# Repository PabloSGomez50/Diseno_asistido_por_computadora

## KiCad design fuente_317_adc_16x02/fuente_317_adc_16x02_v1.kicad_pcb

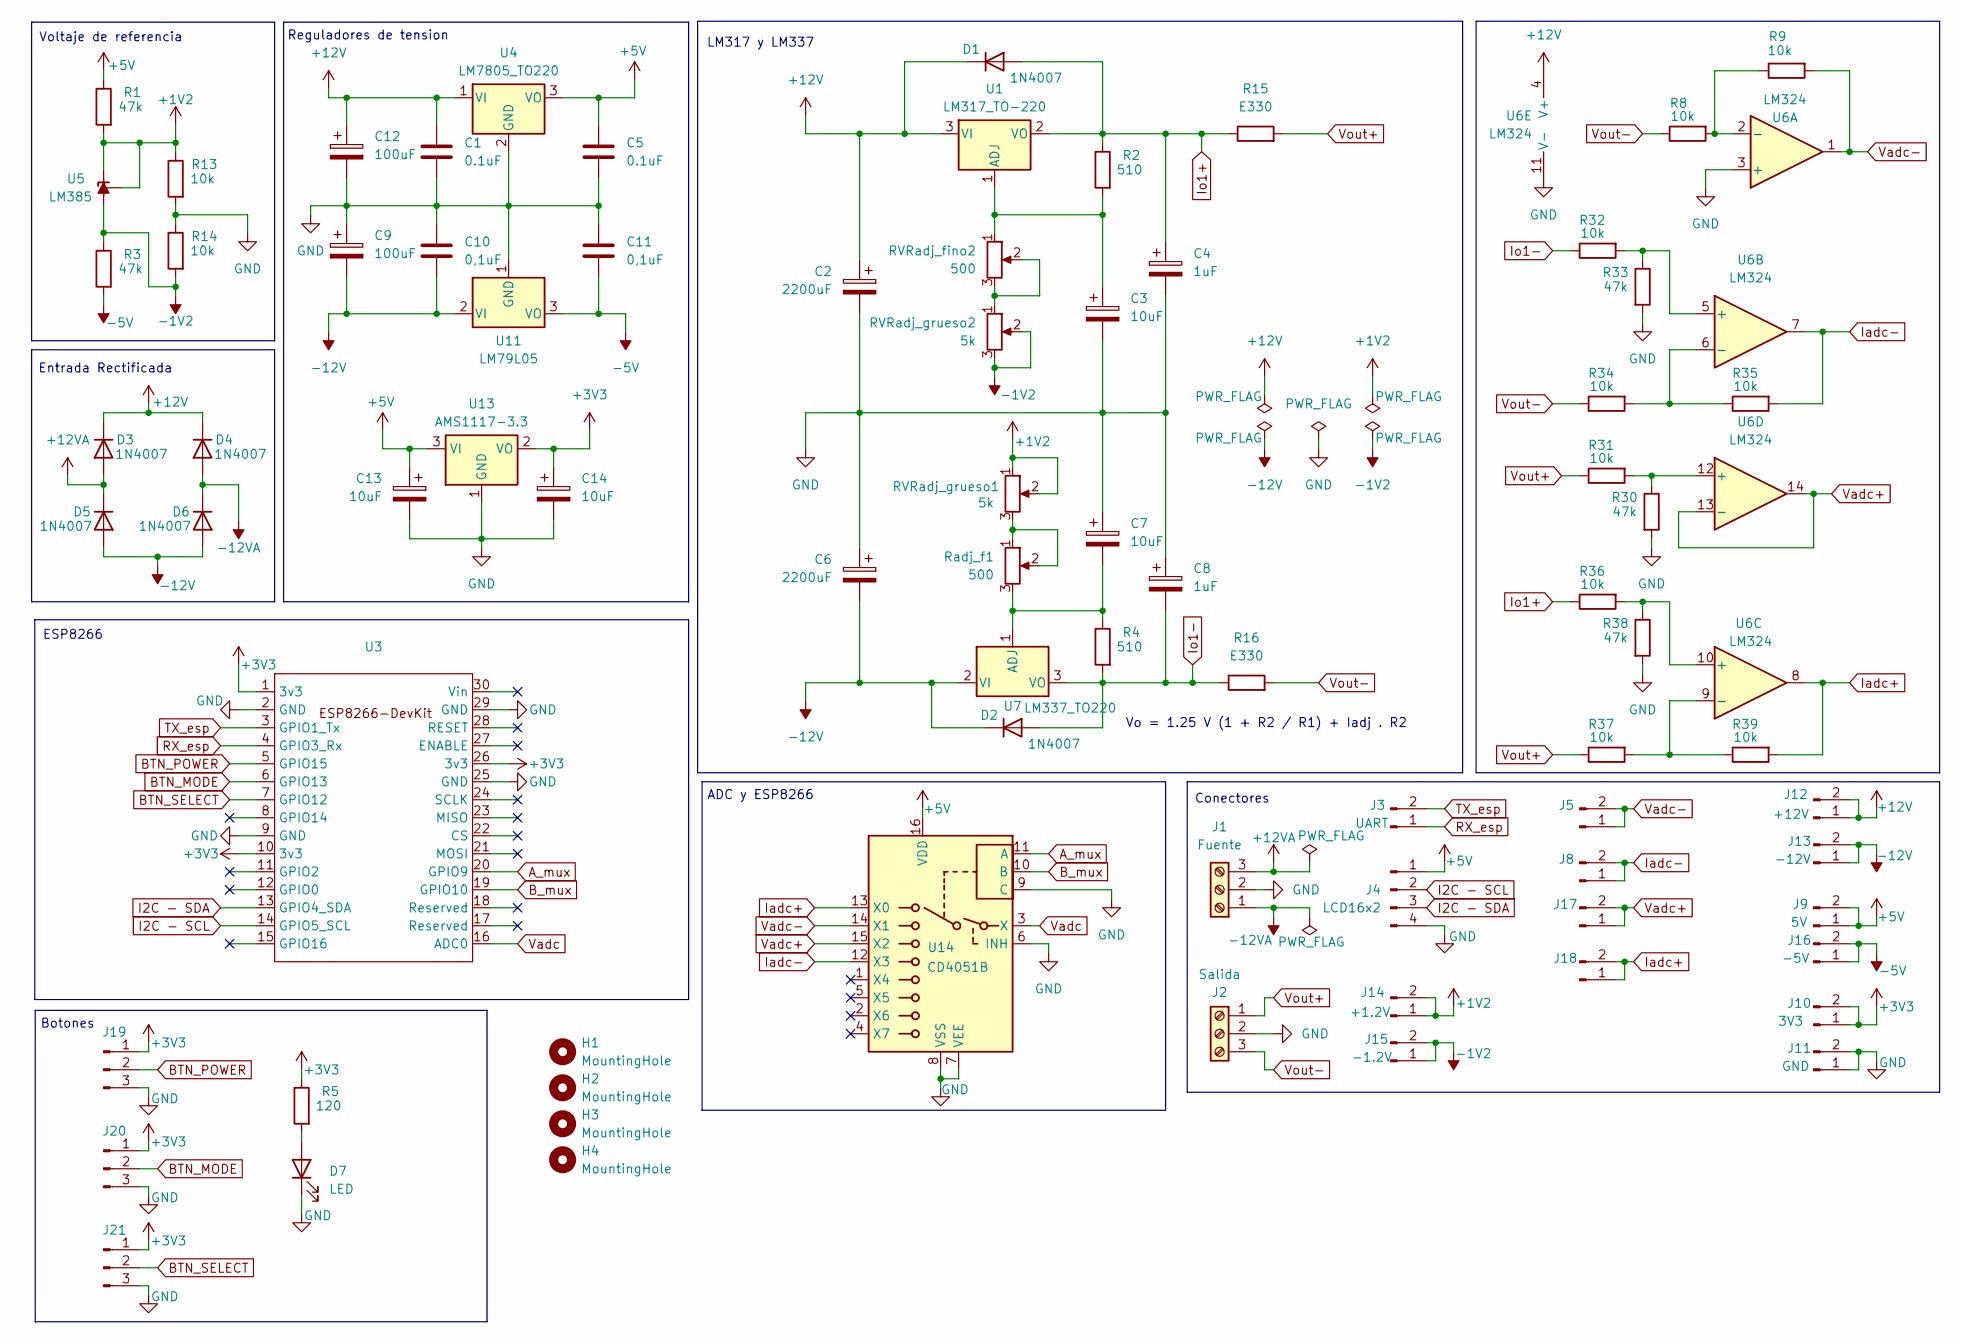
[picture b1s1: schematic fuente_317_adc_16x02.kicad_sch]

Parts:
C1, C5: 0.1uF; C_Disc_D3.0mm_W2.0mm_P2.50mm
C2, C6: 2200uF; CP_Radial_D16.0mm_P7.50mm
C3, C7, C13, C14: 10uF; CP_Radial_D5.0mm_P2.50mm
C4, C8: 1uF; CP_Radial_D5.0mm_P2.50mm
C9, C12: 100uF; CP_Radial_D5.0mm_P2.50mm
C10, C11: 0,1uF; C_Disc_D3.0mm_W2.0mm_P2.50mm
D1, D2, D3, D4, D5, D6: 1N4007; D_DO-41_SOD81_P10.16mm_Horizontal
D7: LED; LED_D5.0mm
H1, H2, H3, H4: MountingHole; MountingHole_3.2mm_M3
J1: Fuente; TerminalBlock_Phoenix_MKDS-1,5-3-5.08_1x03_P5.08mm_Horizont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
J2: Salida; TerminalBlock_Phoenix_MKDS-1,5-3-5.08_1x03_P5.08mm_Horizont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
J3: UART; PinHeader_1x02_P2.54mm_Vertical
J4: LCD16x2; PinHeader_1x04_P2.54mm_Vertical
J5, J17: Vadj+; PinHeader_1x02_P2.54mm_Vertical
J8, J18: Vadj-; PinHeader_1x02_P2.54mm_Vertical
J9: 5V; PinHeader_1x02_P2.54mm_Vertical
J10: 3V3; PinHeader_1x02_P2.54mm_Vertical
J11: GND; PinHeader_1x02_P2.54mm_Vertical
J12: +12V; PinHeader_1x02_P2.54mm_Vertical
J13: -12V; PinHeader_1x02_P2.54mm_Vertical
J14: +1.2V; PinHeader_1x02_P2.54mm_Vertical
J15: -1.2V; PinHeader_1x02_P2.54mm_Vertical
J16: -5V; PinHeader_1x02_P2.54mm_Vertical
J19: BTN_POWER; PinHeader_1x03_P2.54mm_Vertical
J20: BTN_MODE; PinHeader_1x03_P2.54mm_Vertical
J21: BTN_SEL; PinHeader_1x03_P2.54mm_Vertical
R1, R3, R30, R33, R38: 47k; R_Axial_DIN0207_L6.3mm_D2.5mm_P10.16mm_Horizontal
R2, R4: 510; R_Axial_DIN0207_L6.3mm_D2.5mm_P10.16mm_Horizontal
R5: 120; R_Axial_DIN0207_L6.3mm_D2.5mm_P10.16mm_Horizontal
R8, R9, R13, R14, R31, R32, R34, R35, R36, R37, R39: 10k; R_Axial_DIN0207_L6.3mm_D2.5mm_P10.16mm_Horizontal
R15, R16: E330; R_Axial_Power_L25.0mm_W6.4mm_P30.48mm
RVRadj_fino2: 500; PinHeader_1x03_P2.54mm_Vertical
RVRadj_grueso1, RVRadj_grueso2: 5k; PinHeader_1x03_P2.54mm_Vertical
Radj_f1: 500; PinHeader_1x03_P2.54mm_Vertical
U1: LM317_TO-220; TO-220-3_Vertical
U3: Esp-8266-DevKit
U4: LM7805_TO220; TO-220-3_Vertical
U5: LM385; TO-92_Inline
U6: LM324; CERDIP-14_W7.62mm_SideBrazed_Socket
U7: LM337_TO220; TO-220-3_Vertical
U11: LM79L05; TO-92_Inline
U13: AMS1117-3.3; SOT-223-3_TabPin2
U14: CD4051B; CERDIP-16_W7.62mm_SideBrazed_Socket

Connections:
+1V2: J14.1, J14.2, R1.2, R13.1, RVRadj_grueso1.1, RVRadj_grueso1.2, U5.1 (REF), U5.3 (K)
+3V3: C14.1, J10.1, J10.2, J19.1, J20.1, J21.1, R5.1, U3.1 (3v3), U3.10 (3v3), U3.26 (3v3), U13.2 (VO)
+5V: C5.1, C13.1, J4.1, J9.1, J9.2, R1.1, U4.3 (VO), U13.3 (VI), U14.16 (VDD)
+12V: C1.1, C2.1, C12.1, D1.1 (K), D3.1 (K), D4.1 (K), J12.1, J12.2, U1.3 (VI), U4.1 (VI), U6.4 (V+)
+12VA: D3.2 (A), D5.1 (K), J1.3
-1V2: J15.1, J15.2, R3.1, R14.2, RVRadj_grueso2.2, RVRadj_grueso2.3, U5.2 (A)
-5V: C11.2, J16.1, J16.2, R3.2, U11.3 (VO)
-12V: C6.2, C9.2, C10.2, D2.1 (K), D5.2 (A), D6.2 (A), J13.1, J13.2, U7.2 (VI), U11.2 (VI)
-12VA: D4.2 (A), D6.1 (K), J1.1
A_mux: U3.20 (GPIO9), U14.11 (A)
BTN_MODE: J20.2, U3.6 (GPIO13)
BTN_POWER: J19.2, U3.5 (GPIO15)
BTN_SELECT: J21.2, U3.7 (GPIO12)
B_mux: U3.19 (GPIO10), U14.10 (B)
GND: C1.2, C2.2, C3.2, C4.2, C5.2, C6.1, C7.1, C8.1, C9.1, C10.1, C11.1, C12.2, C13.2, C14.2, D7.1 (K), J1.2, J2.2, J4.4, J11.1, J11.2, J19.3, J20.3, J21.3, R13.2, R14.1, R30.2, R33.2, R38.2, U3.2 (GND), U3.9 (GND), U3.25 (GND), U3.29 (GND), U4.2 (GND), U6.3 (+), U6.11 (V-), U11.1 (GND), U13.1 (GND), U14.6 (INH), U14.7 (VEE), U14.8 (VSS), U14.9 (C)
I2C - SCL: J4.2, U3.14 (GPIO5_SCL)
I2C - SDA: J4.3, U3.13 (GPIO4_SDA)
Iadc+: J18.1, J18.2, R39.2, U6.8, U14.13 (X0)
Iadc-: J8.1, J8.2, R35.2, U6.7, U14.12 (X3)
Io1+: C4.1, D1.2 (A), R2.1, R15.1, R36.1, U1.2 (VO)
Io1-: C8.2, D2.2 (A), R4.2, R16.1, R32.1, U7.3 (VO)
unnamed: D7.2 (A), R5.2
unnamed: RVRadj_fino2.2, RVRadj_fino2.3, RVRadj_grueso2.1
unnamed: RVRadj_grueso1.3, Radj_f1.1, Radj_f1.2
unnamed: C3.1, R2.2, RVRadj_fino2.1, U1.1 (ADJ)
unnamed: R8.2, R9.1, U6.2 (-)
unnamed: R32.2, R33.1, U6.5 (+)
unnamed: R34.2, R35.1, U6.6 (-)
unnamed: R36.2, R38.1, U6.10 (+)
unnamed: R37.2, R39.1, U6.9 (-)
unnamed: R30.1, R31.2, U6.12 (+)
unnamed: C7.2, R4.1, Radj_f1.3, U7.1 (ADJ)
RX_esp: J3.1, U3.4 (GPIO3_Rx)
TX_esp: J3.2, U3.3 (GPIO1_Tx)
Vadc: U3.16 (ADC0), U14.3 (X)
Vadc+: J17.1, J17.2, U6.13 (-), U6.14, U14.15 (X2)
Vadc-: J5.1, J5.2, R9.2, U6.1, U14.14 (X1)
Vout+: J2.1, R15.2, R31.1, R37.1
Vout-: J2.3, R8.1, R16.2, R34.1

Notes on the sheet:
Reguladores de tension
Voltaje de referencia
LM317 y LM337
ESP8266
Botones
Entrada Rectificada
Vo = 1.25 V (1 + R2 / R1) + Iadj . R2
Conectores
ADC y ESP8266

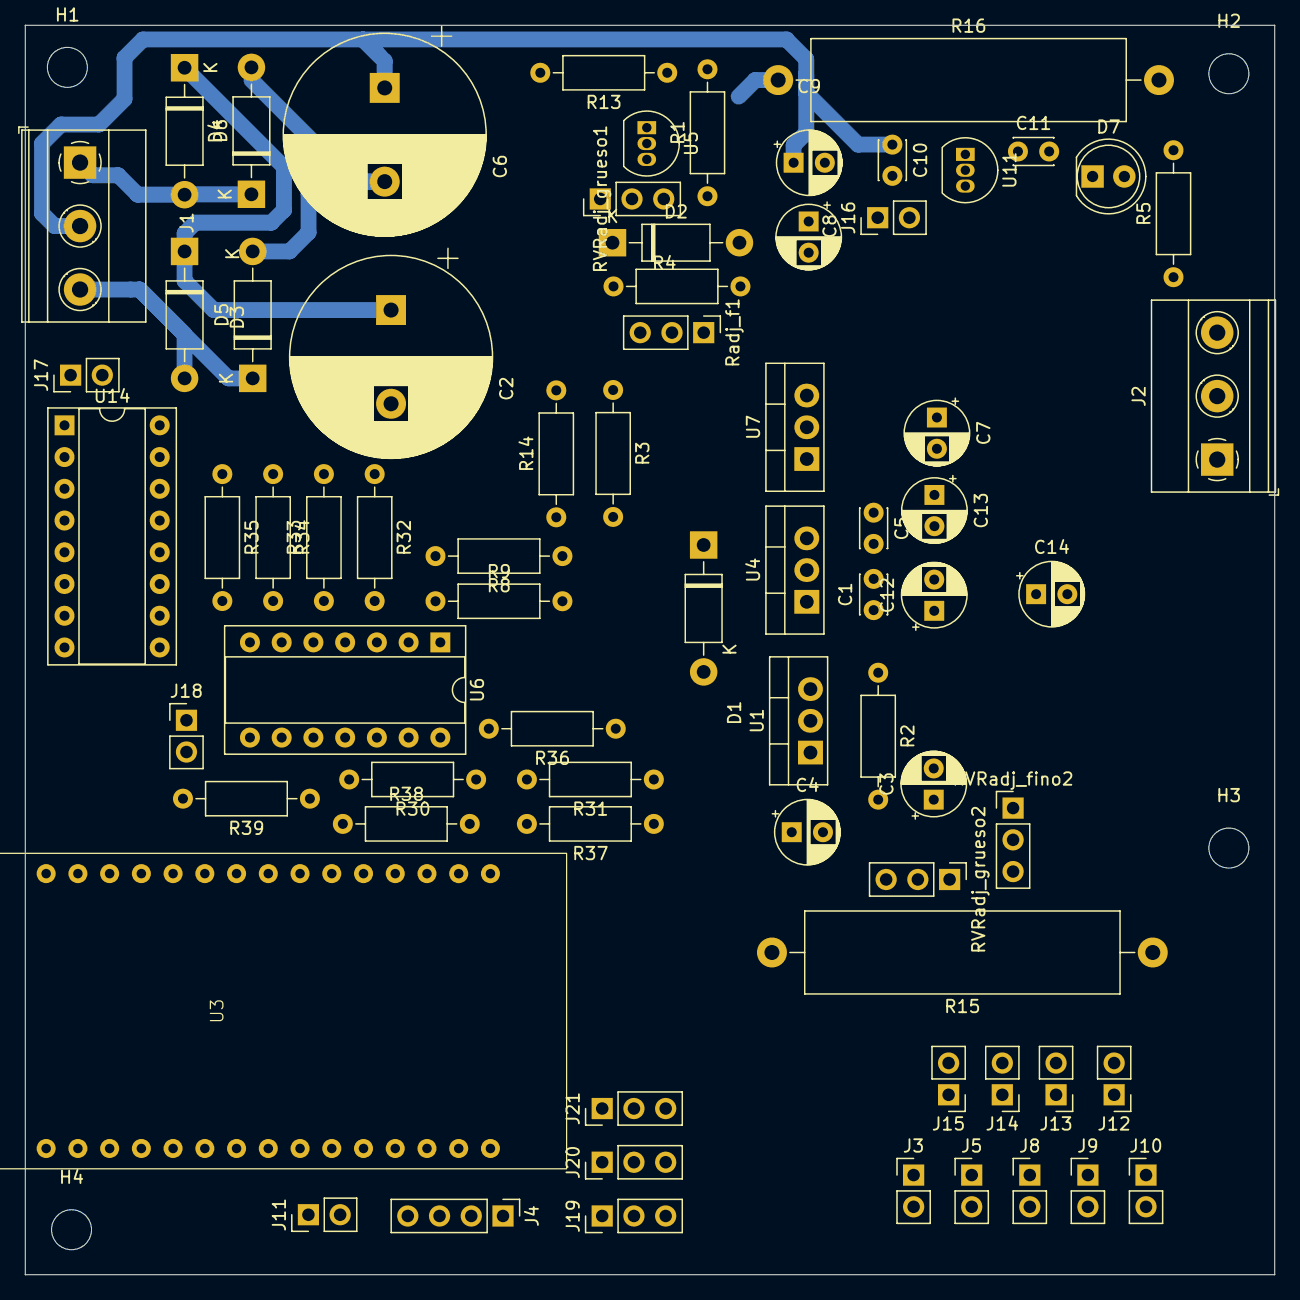
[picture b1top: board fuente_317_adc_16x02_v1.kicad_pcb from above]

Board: 2 copper layers, 100.0 x 100.0 mm, 78 parts (1 on the bottom side), 39 nets.
